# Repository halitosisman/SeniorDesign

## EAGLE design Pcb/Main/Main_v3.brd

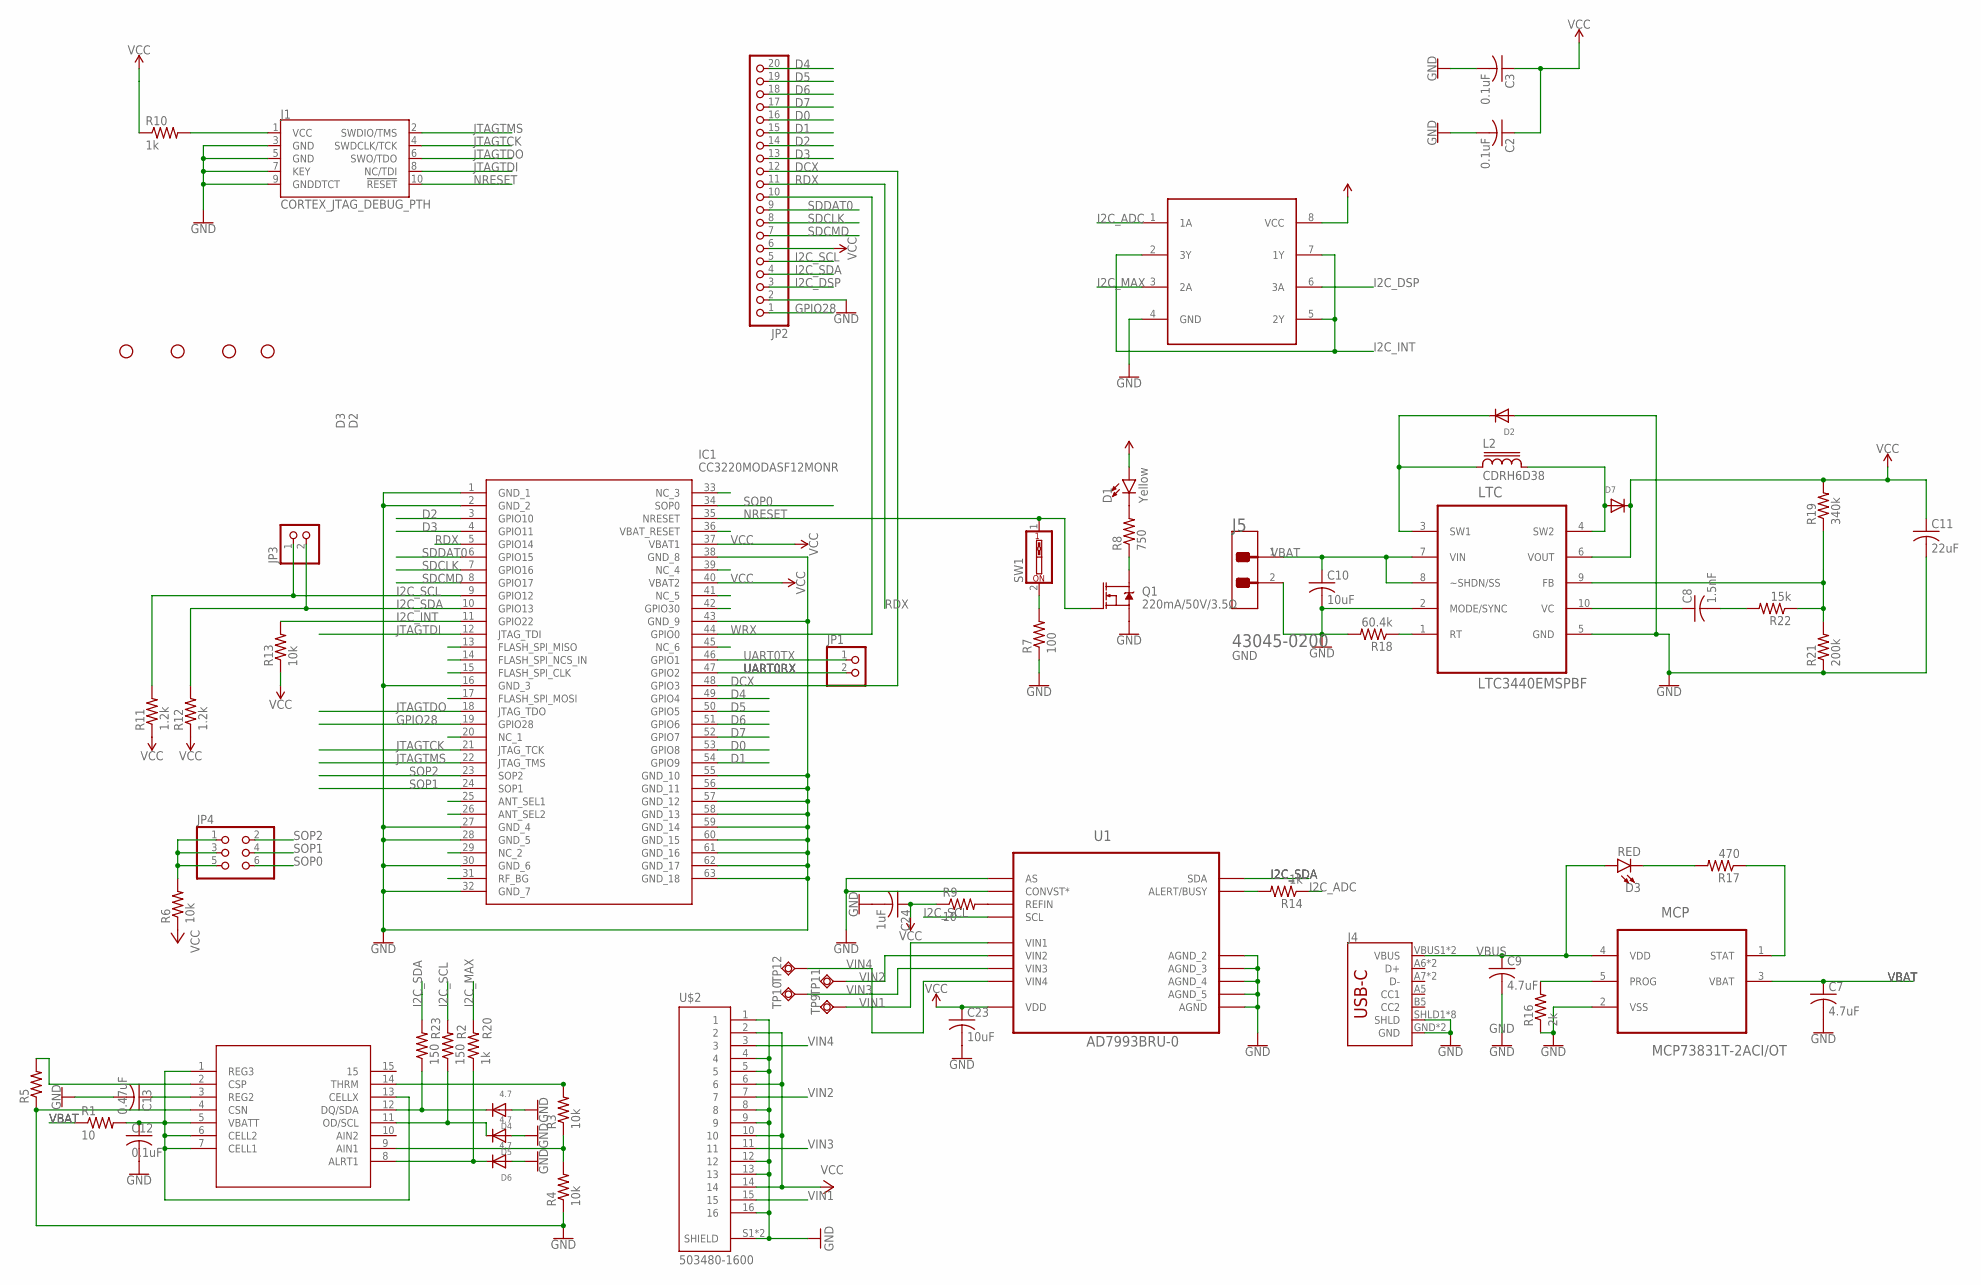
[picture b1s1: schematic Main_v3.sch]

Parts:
74LVC: SOP65P400X110-8N
C2, C3, C12: 0.1uF; C0805
C7, C9: 4.7uF; C0805
C8: 1.5nF; C0805
C10, C23: 10uF; C0805
C11: 22uF; C1210
C13: 0.47uF; C0805
C24: 1uF; C0805
D1: Yellow; LED-0603
D2, D7: DIODESOD-323F; SOD-323F
D3: RED; LED-0603
D4, D5, D6: 4.7; SOD-323F
H1, H2, H3, H4: STAND-OFF
IC1: CC3220MODASF12MONR; CC3220MODASM2MONR
J1: CORTEX_JTAG_DEBUG_PTH; 2X5-PTH-1.27MM
J4: USB_C2-LAYER; USB-C-16P
J5: MOLEX_43045-0200MOLEX_43045-0200_0_0; MOLEX_43045-0200_0
JP1, JP3: PINHD-1X2; 1X02
JP2: PINHD-1X20; 1X20
JP4: PINHD-2X3; 2X03
L2: CDRH6D38; CDRH6D
LTC: LTC3440EMSPBF; SOP50P490X110-10N
MAX: MAX17201G+T; 21-0137I_T1433-1
MCP: MCP73831T-2ACI/OT; SOT95P280X145-5N
Q1: 220mA/50V/3.5Ω; SOT23-3
R1, R9: 10; R0805
R2, R23: 150; R0805
R3, R4, R6, R13: 10k; R0805
R5: R-US_R0805; R0805
R7: 100; R0805
R8: 750; R0805
R10, R14, R20: 1k; R0805
R11, R12: 1.2k; R0805
R16: 2k; R0805
R17: 470; R0805
R18: 60.4k; R0805
R19: 340k; R0805
R21: 200k; R0805
R22: 15k; R0805
SW1: SW_DIP-1; EDG-01
TP9, TP10, TP11, TP12: TPSQTP12R; TP12R
U1: AD7993BRU-0; SOP65P640X120-16N
U$2: 503480-1600; MOLEX_503480-1600

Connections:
D0: IC1.53 (GPIO8), JP2.16
D1: IC1.54 (GPIO9), JP2.15
D2: IC1.3 (GPIO10), JP2.14
D3: IC1.4 (GPIO11), JP2.13
D4: IC1.49 (GPIO4), JP2.20
D5: IC1.50 (GPIO5), JP2.19
D6: IC1.51 (GPIO6), JP2.18
D7: IC1.52 (GPIO7), JP2.17
DCX: IC1.48 (GPIO3), JP2.12
GND: 74LVC.4 (GND), C2.2, C3.2, C7.2, C9.2, C10.2, C11.2, C12.2, C13.2, C23.2, C24.2, D2.A, D4.A, D5.A, D6.A, IC1.1 (GND_1), IC1.2 (GND_2), IC1.16 (GND_3), IC1.27 (GND_4), IC1.28 (GND_5), IC1.30 (GND_6), IC1.32 (GND_7), IC1.38 (GND_8), IC1.43 (GND_9), IC1.55 (GND_10), IC1.56 (GND_11), IC1.57 (GND_12), IC1.58 (GND_13), IC1.59 (GND_14), IC1.60 (GND_15), IC1.61 (GND_16), IC1.62 (GND_17), IC1.63 (GND_18), J1.3 (GND), J1.5 (GND), J1.7 (KEY), J1.9 (GNDDTCT), J4.GND, J4.GND2 (GND), J4.SHLD1 (SHLD), J4.SHLD2 (SHLD), J4.SHLD3 (SHLD), J4.SHLD4 (SHLD), J4.SHLD5 (SHLD), J4.SHLD6 (SHLD), J4.SHLD7 (SHLD), J4.SHLD8 (SHLD), J5.2, JP2.2, LTC.2 (MODE/SYNC), LTC.5 (GND), MAX.4 (CSN), MCP.2 (VSS), Q1.2 (S), R4.1, R5.1, R7.1, R16.1, R18.2, R21.1, U1.1 (AGND_2), U1.2 (AGND_3), U1.3 (AGND_4), U1.4 (AGND_5), U1.11 (AS), U1.12 (CONVST*), U1.16 (AGND), U$2.1, U$2.4, U$2.5, U$2.8, U$2.9, U$2.12, U$2.13, U$2.16, U$2.S1 (SHIELD), U$2.S2 (SHIELD)
GPIO28: IC1.19 (GPIO28), JP2.1
I2C_ADC: 74LVC.1 (1A), R14.1
I2C_DSP: 74LVC.6 (3A), JP2.3
I2C_INT: 74LVC.2 (3Y), 74LVC.5 (2Y), 74LVC.7 (1Y), IC1.11 (GPIO22), R13.2
I2C_MAX: 74LVC.3 (2A), R20.2
I2C_SCL: IC1.9 (GPIO12), JP2.5, JP3.1, R2.2, R11.2, U1.15 (SCL)
I2C_SDA: IC1.10 (GPIO13), JP2.4, JP3.2, R12.2, R23.2, U1.14 (SDA)
JTAGTCK: IC1.21 (JTAG_TCK), J1.4 (SWDCLK/TCK)
JTAGTDI: IC1.12 (JTAG_TDI), J1.8 (NC/TDI)
JTAGTDO: IC1.18 (JTAG_TDO), J1.6 (SWO/TDO)
JTAGTMS: IC1.22 (JTAG_TMS), J1.2 (SWDIO/TMS)
JTAG_R: J1.1 (VCC), R10.2
LTC_CRS: C8.2, R22.2
LTC_FB: LTC.9 (FB), R19.1, R21.2, R22.1
LTC_IND1: D2.C, L2.1, LTC.3 (SW1)
LTC_IND2: D7.A, L2.2, LTC.4 (SW2)
LTC_RT: LTC.1 (RT), R18.1
LTC_VC: C8.1, LTC.10 (VC)
MAX_AIN1: MAX.9 (AIN1), R3.1, R4.2
MAX_CSP: MAX.2 (CSP), R5.2
MAX_INT: D6.C, MAX.8 (ALRT1), R20.1
MAX_REG2: C13.1, MAX.3 (REG2)
MAX_SCL: D5.C, MAX.11 (OD/SCL), R2.1
MAX_SDA: D4.C, MAX.12 (DQ/SDA), R23.1
MAX_THRM: MAX.14 (THRM), R3.2
MAX_VBAT: C12.1, MAX.1 (REG3), MAX.5 (VBATT), MAX.6 (CELL2), MAX.7 (CELL1), MAX.13 (CELLX), R1.2
MPC_LED: D3.C, R17.2
MPC_RPROG: MCP.5 (PROG), R16.2
MPC_STAT: MCP.1 (STAT), R17.1
unnamed: JP4.1, JP4.3, JP4.5, R6.2
unnamed: R9.2, U1.6 (REFIN)
unnamed: R14.2, U1.13 (ALERT/BUSY)
NRESET: IC1.35 (NRESET), J1.10 (!RESET), Q1.1 (G), SW1.1
RDX: IC1.5 (GPIO14), JP2.11
RESET_DIODE: D1.C, R8.2
RESET_MOS: Q1.3 (D), R8.1
RESET_SW1: R7.2, SW1.2
SDCLK: IC1.7 (GPIO16), JP2.8
SDCMD: IC1.8 (GPIO17), JP2.7
SDDAT0: IC1.6 (GPIO15), JP2.9
SOP0: IC1.34 (SOP0), JP4.6
SOP1: IC1.24 (SOP1), JP4.4
SOP2: IC1.23 (SOP2), JP4.2
UART0RX: IC1.47 (GPIO2), JP1.2
UART0TX: IC1.46 (GPIO1), JP1.1
VBAT: C7.1, C10.1, J5.1, LTC.7 (VIN), LTC.8 (~SHDN/SS), MCP.3 (VBAT), R1.1
VBUS: C9.1, D3.A, J4.VBUS1 (VBUS), J4.VBUS2 (VBUS), MCP.4 (VDD)
VCC: 74LVC.8 (VCC), C2.1, C3.1, C11.1, C23.1, C24.1, D1.A, D7.C, IC1.37 (VBAT1), IC1.40 (VBAT2), JP2.6, LTC.6 (VOUT), R6.1, R9.1, R10.1, R11.1, R12.1, R13.1, R19.2, U1.5 (VDD), U$2.2, U$2.6, U$2.10, U$2.14
VIN1: TP9.TP, U1.7 (VIN1), U$2.15
VIN2: TP11.TP, U1.10 (VIN2), U$2.7
VIN3: TP10.TP, U1.8 (VIN3), U$2.11
VIN4: TP12.TP, U1.9 (VIN4), U$2.3
WRX: IC1.44 (GPIO0), JP2.10

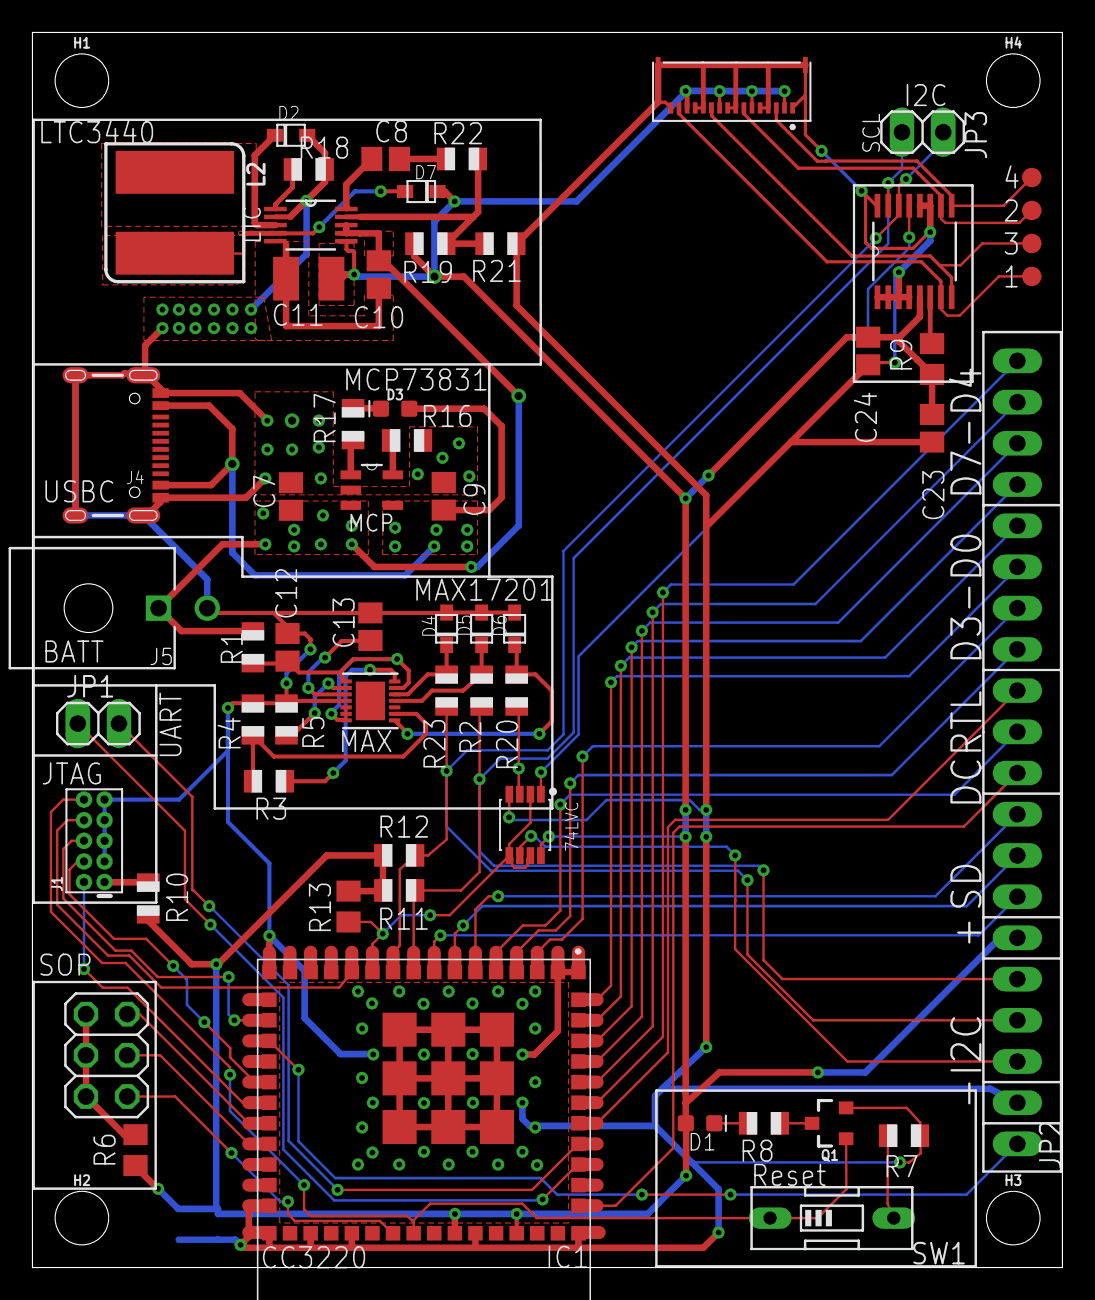
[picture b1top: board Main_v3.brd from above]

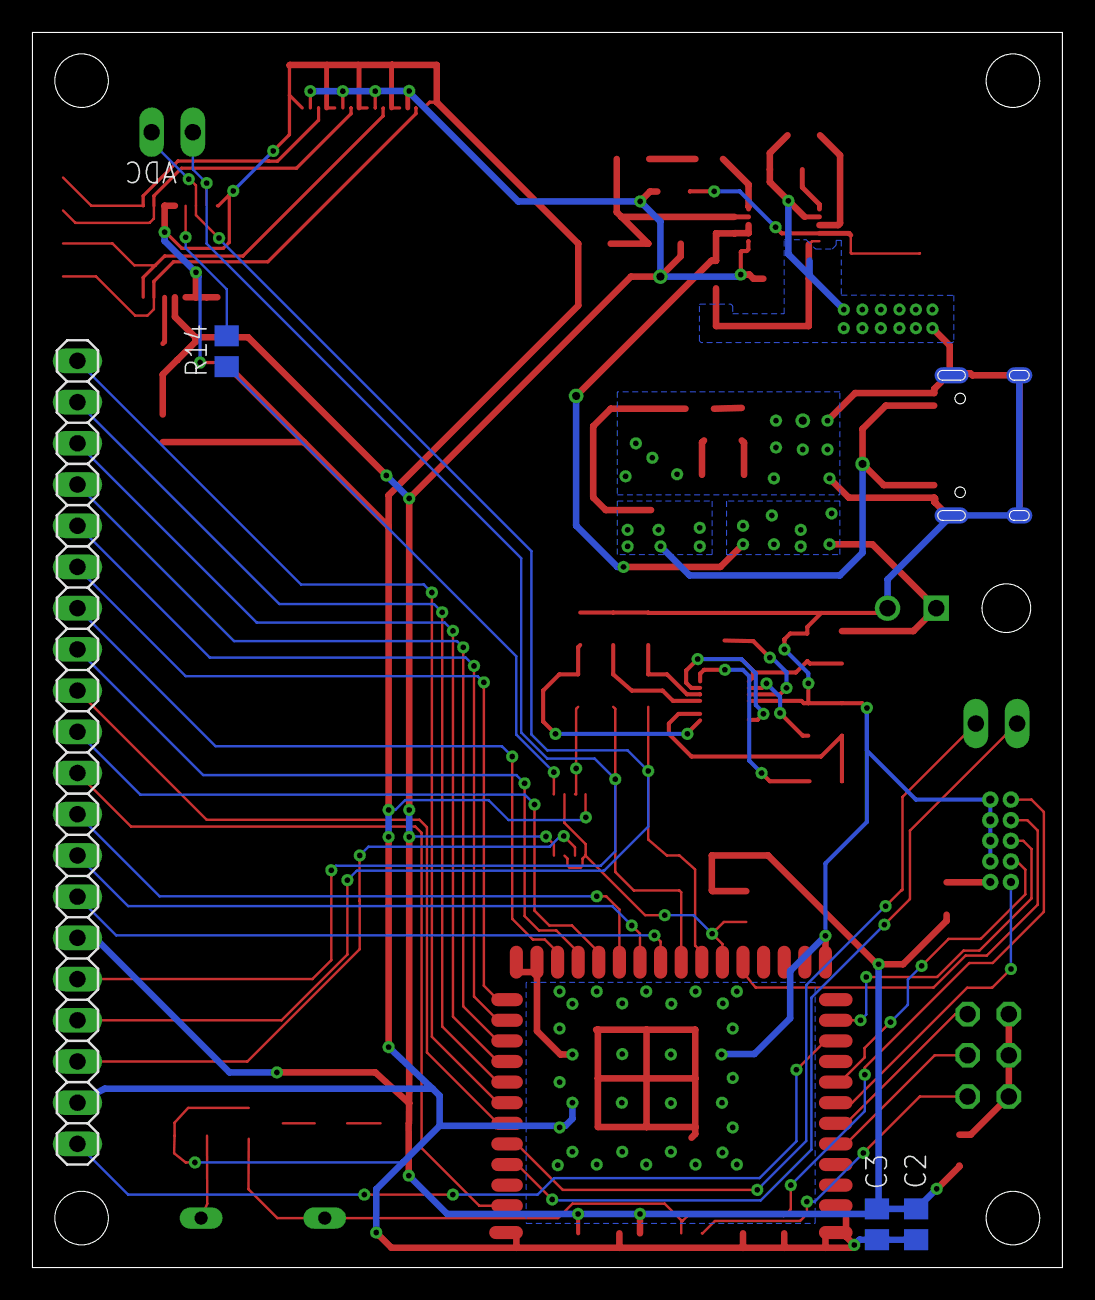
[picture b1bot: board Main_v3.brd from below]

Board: 2 copper layers, 63.5 x 76.1 mm, 65 parts (4 on the bottom side), 63 nets.

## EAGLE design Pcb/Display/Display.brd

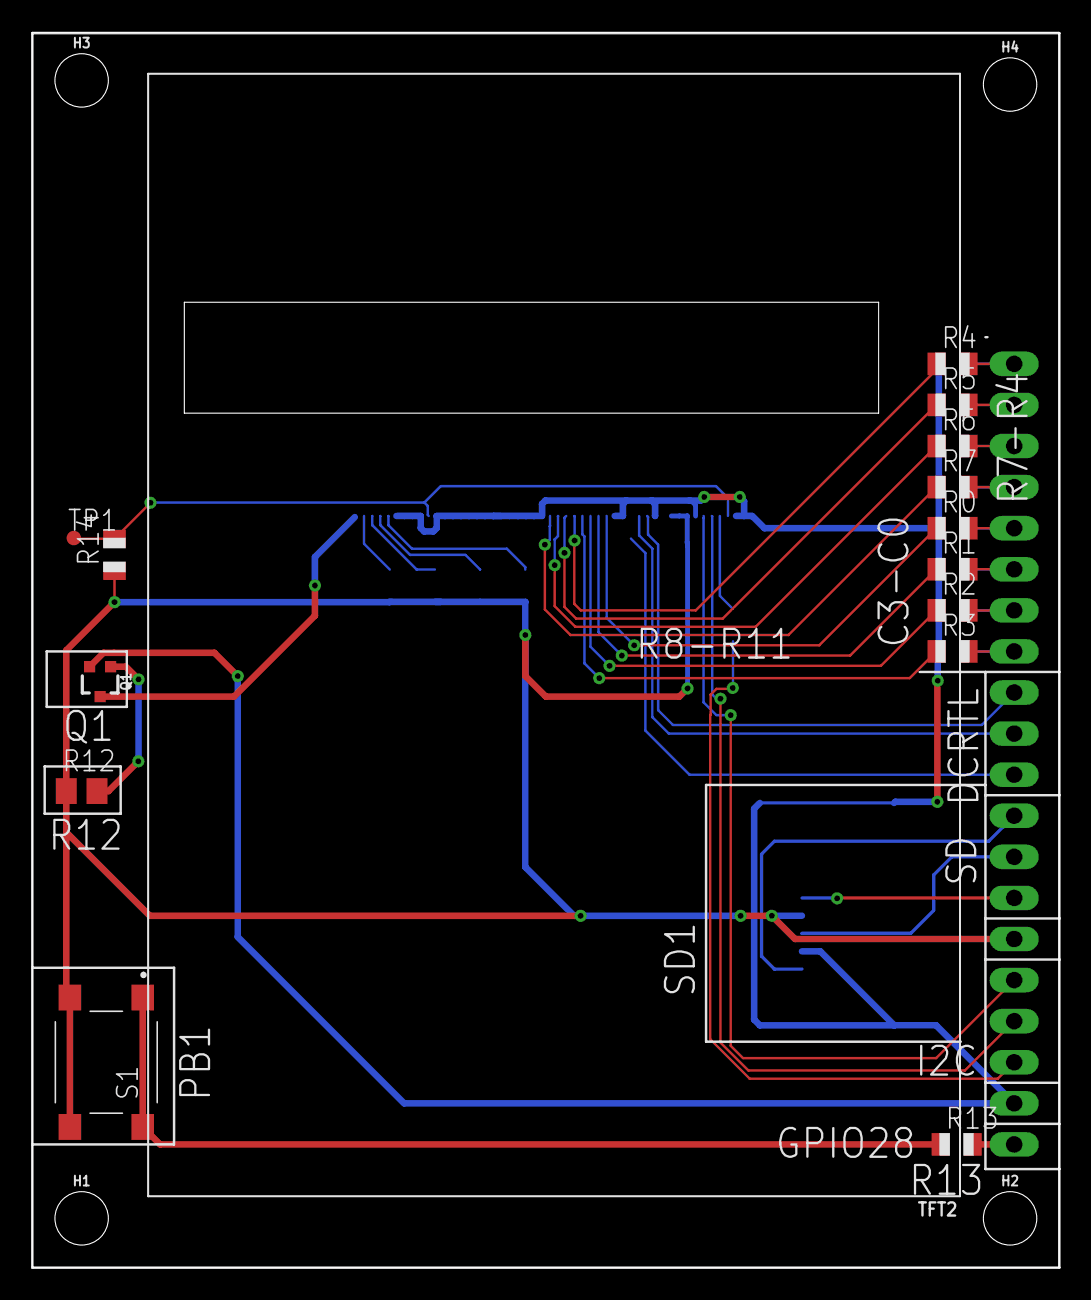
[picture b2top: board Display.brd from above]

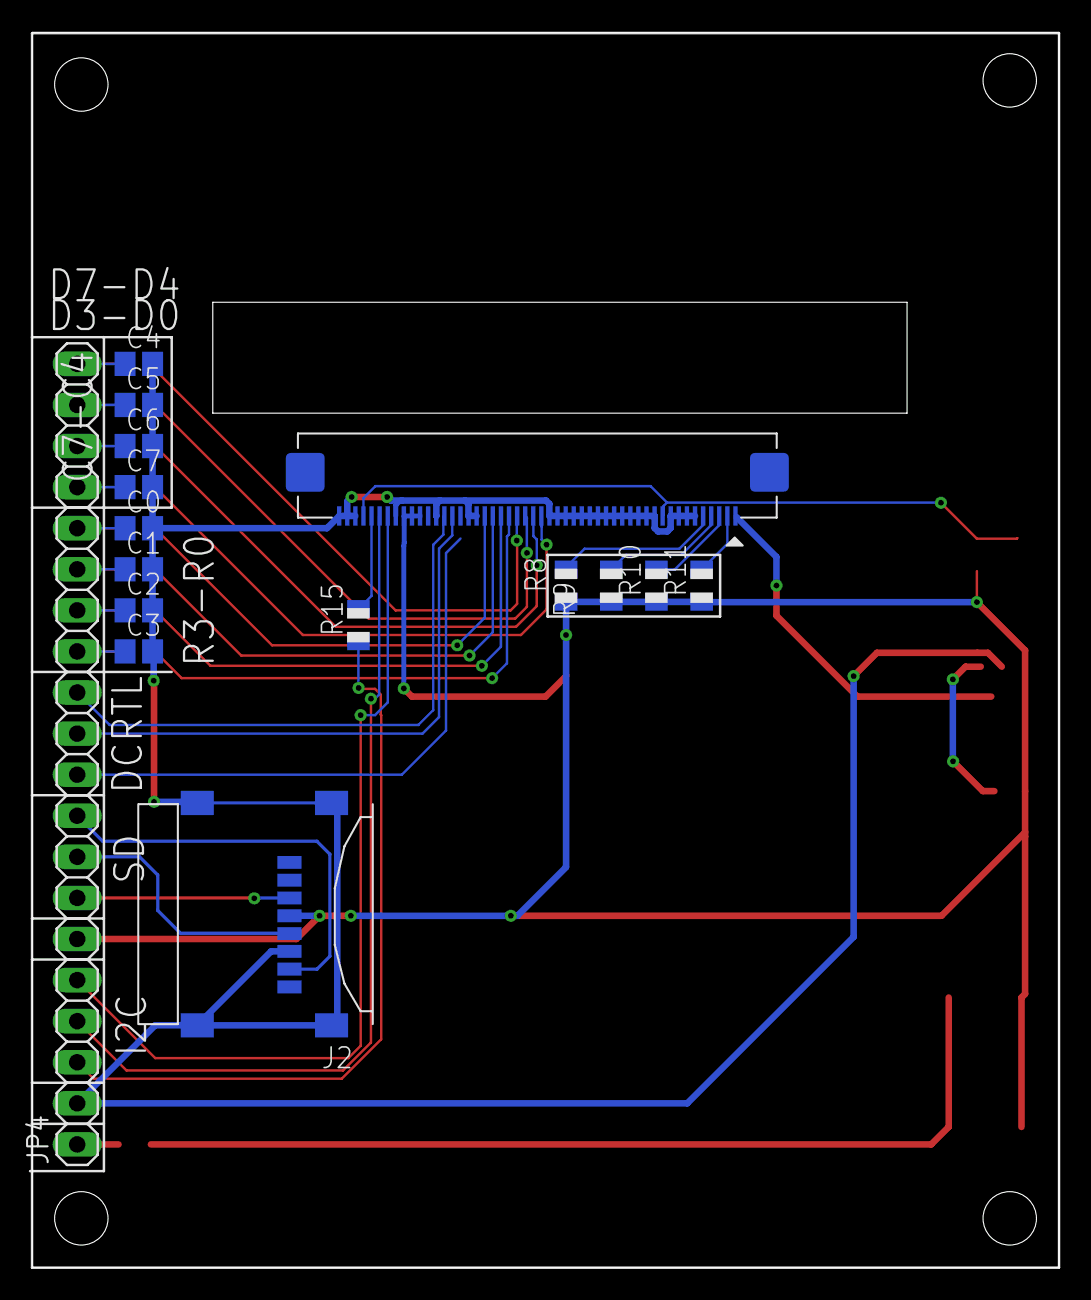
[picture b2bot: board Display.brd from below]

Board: 2 copper layers, 63.5 x 76.4 mm, 34 parts (15 on the bottom side), 37 nets.

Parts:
C0, C1, C2, C3, C4, C5, C6, C7: 10pF; C0805
H1, H2, H3, H4: STAND-OFF
J2: 47219-2001; MOLEX_47219-2001
JP4: Main PCB Header; 1X20
Q1: 310mA/60V/1.6Ω; SOT323
R0, R1, R2, R3, R4, R5, R6, R7, R8, R9, R10, R11, R14: 10; R0805
R12: 2.2k; M0805
R13: 100; R0805
R15: 1k; R0805
S1: B3FS-1000; B3FS1000
TFT2: TFT_CTP28
TP1: TPTP09R; TP09R

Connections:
DB0: C0.1, JP4.16, R0.2
DB1: C1.1, JP4.15, R1.2
DB2: C2.1, JP4.14, R2.2
DB3: C3.1, JP4.13, R3.2
DB4: C4.1, JP4.20, R4.2
DB5: C5.1, JP4.19, R5.2
DB6: C6.1, JP4.18, R6.2
DB7: C7.1, JP4.17, R7.2
DCX: JP4.12, TFT2.37
GND: C0.2, C1.2, C2.2, C3.2, C4.2, C5.2, C6.2, C7.2, J2.6, J2.G1, J2.G2, J2.G3, J2.G4, JP4.2, Q1.2, TFT2.6, TFT2.7, TFT2.8, TFT2.9, TFT2.11, TFT2.12, TFT2.13, TFT2.14, TFT2.15, TFT2.16, TFT2.17, TFT2.18, TFT2.19, TFT2.20, TFT2.21, TFT2.22, TFT2.23, TFT2.24, TFT2.33, TFT2.34, TFT2.38, TFT2.43, TFT2.48, TFT2.49, TFT2.50
GPIO28: JP4.1, R13.2
I2C_INT: JP4.3, R15.1
I2C_SCL: JP4.5, TFT2.44
I2C_SDA: JP4.4, TFT2.45
unnamed: R0.1, TFT2.32
unnamed: R1.1, TFT2.31
unnamed: R2.1, TFT2.30
unnamed: R15.2, TFT2.46
unnamed: R3.1, TFT2.29
unnamed: R4.1, TFT2.28
unnamed: R5.1, TFT2.27
unnamed: R7.1, TFT2.25
unnamed: R6.1, TFT2.26
unnamed: Q1.1, R12.2
R8: R8.2, TFT2.5
R9: R9.2, TFT2.4
R10: R10.2, TFT2.3
R11: R11.2, TFT2.2
R12: Q1.3, TFT2.1
R13: R13.1, S1.1, S1.2
RDX: JP4.11, TFT2.35
RST: R14.2, TFT2.10, TFT2.47, TP1.TP
SD_CLK: J2.5, JP4.8
SD_CMD: J2.3, JP4.7
SD_DAT0: J2.7, JP4.9
VCC: J2.4, JP4.6, R8.1, R9.1, R10.1, R11.1, R12.1, R14.1, S1.3, S1.4, TFT2.40, TFT2.41, TFT2.42
WRX: JP4.10, TFT2.36

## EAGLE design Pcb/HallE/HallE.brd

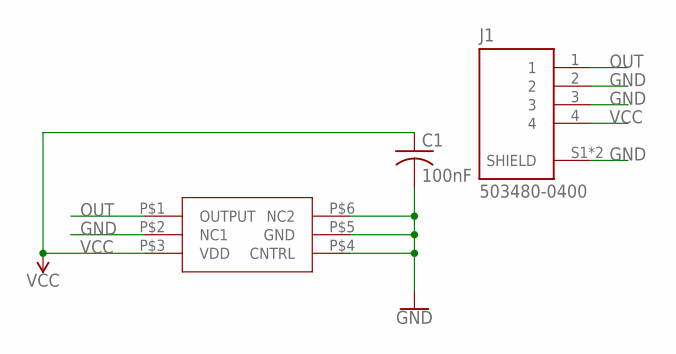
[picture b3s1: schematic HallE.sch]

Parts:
C1: 100nF; C0805
J1: 503480-0400; MOLEX_503480-0400
U$1: AH8503; UDFN-6

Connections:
GND: C1.2, J1.2, J1.3, J1.S1 (SHIELD), J1.S2 (SHIELD), U$1.P$2 (NC1), U$1.P$4 (CNTRL), U$1.P$5 (GND), U$1.P$6 (NC2)
OUT: J1.1, U$1.P$1 (OUTPUT)
VCC: C1.1, J1.4, U$1.P$3 (VDD)

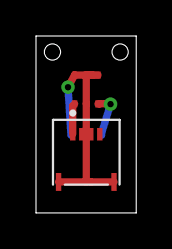
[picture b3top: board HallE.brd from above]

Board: 2 copper layers, 5.6 x 9.8 mm, 3 parts (1 on the bottom side), 3 nets.

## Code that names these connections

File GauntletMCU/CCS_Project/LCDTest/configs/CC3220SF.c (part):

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PowerCC32XX_ParkInfo parkInfo[] = {
/*          PIN                    PARK STATE              PIN ALIAS (FUNCTION)
     -----------------  ------------------------------     -------------------- */
    {PowerCC32XX_PIN01, PowerCC32XX_WEAK_PULL_DOWN_STD}, /* GPIO10              */
    {PowerCC32XX_PIN02, PowerCC32XX_WEAK_PULL_DOWN_STD}, /* GPIO11              */
    {PowerCC32XX_PIN03, PowerCC32XX_WEAK_PULL_DOWN_STD}, /* GPIO12              */
    {PowerCC32XX_PIN04, PowerCC32XX_WEAK_PULL_DOWN_STD}, /* GPIO13              */
    {PowerCC32XX_PIN05, PowerCC32XX_WEAK_PULL_DOWN_STD}, /* GPIO14              */
    {PowerCC32XX_PIN06, PowerCC32XX_WEAK_PULL_DOWN_STD}, /* GPIO15              */
    {PowerCC32XX_PIN07, PowerCC32XX_WEAK_PULL_DOWN_STD}, /* GPIO16              */
    {PowerCC32XX_PIN08, PowerCC32XX_WEAK_PULL_DOWN_STD}, /* GPIO17              */
    {PowerCC32XX_PIN13, PowerCC32XX_WEAK_PULL_DOWN_STD}, /* FLASH_SPI_DIN       */
    {PowerCC32XX_PIN15, PowerCC32XX_WEAK_PULL_DOWN_STD}, /* GPIO22              */
    {PowerCC32XX_PIN16, PowerCC32XX_WEAK_PULL_DOWN_STD}, /* TDI (JTAG DEBUG)    */
    {PowerCC32XX_PIN17, PowerCC32XX_WEAK_PULL_DOWN_STD}, /* TDO (JTAG DEBUG)    */
    {PowerCC32XX_PIN19, PowerCC32XX_WEAK_PULL_DOWN_STD}, /* TCK (JTAG DEBUG)    */
    {PowerCC32XX_PIN20, PowerCC32XX_WEAK_PULL_DOWN_STD}, /* TMS (JTAG DEBUG)    */
    {PowerCC32XX_PIN18, PowerCC32XX_WEAK_PULL_DOWN_STD}, /* GPIO28              */
    {PowerCC32XX_PIN21, PowerCC32XX_WEAK_PULL_DOWN_STD}, /* SOP2                */
    {PowerCC32XX_PIN29, PowerCC32XX_WEAK_PULL_DOWN_STD}, /* ANTSEL1             */
    {PowerCC32XX_PIN30, PowerCC32XX_WEAK_PULL_DOWN_STD}, /* ANTSEL2             */
    {PowerCC32XX_PIN45, PowerCC32XX_WEAK_PULL_DOWN_STD}, /* DCDC_ANA2_SW_P      */
    {PowerCC32XX_PIN50, PowerCC32XX_WEAK_PULL_DOWN_STD}, /* GPIO0               */
    {PowerCC32XX_PIN52, PowerCC32XX_WEAK_PULL_DOWN_STD}, /* RTC_XTAL_N          */
    {PowerCC32XX_PIN53, PowerCC32XX_WEAK_PULL_DOWN_STD}, /* GPIO30              */
    {PowerCC32XX_PIN55, PowerCC32XX_WEAK_PULL_UP_STD},   /* GPIO1 (XDS_UART_RX) */
    {PowerCC32XX_PIN57, PowerCC32XX_WEAK_PULL_UP_STD},   /* GPIO2 (XDS_UART_TX) */
    {PowerCC32XX_PIN58, PowerCC32XX_WEAK_PULL_DOWN_STD}, /* GPIO3               */
    {PowerCC32XX_PIN59, PowerCC32XX_WEAK_PULL_DOWN_STD}, /* GPIO4               */
    {PowerCC32XX_PIN60, PowerCC32XX_WEAK_PULL_DOWN_STD}, /* GPIO5               */
    {PowerCC32XX_PIN61, PowerCC32XX_WEAK_PULL_DOWN_STD}, /* GPIO6               */
    {PowerCC32XX_PIN62, PowerCC32XX_WEAK_PULL_DOWN_STD}, /* GPIO7               */
    {PowerCC32XX_PIN63, PowerCC32XX_WEAK_PULL_DOWN_STD}, /* GPIO8               */
    {PowerCC32XX_PIN64, PowerCC32XX_WEAK_PULL_DOWN_STD}, /* GPIO9               */
};

/*
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
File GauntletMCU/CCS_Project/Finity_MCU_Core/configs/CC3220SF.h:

/*
 * Copyright (c) 2016-2018, Texas Instruments Incorporated
 * All rights reserved.
 *
 * Redistribution and use in source and binary forms, with or without
 * modification, are permitted provided that the following conditions
 * are met:
 *
 * *  Redistributions of source code must retain the above copyright
 *    notice, this list of conditions and the following disclaimer.
 *
 * *  Redistributions in binary form must reproduce the above copyright
 *    notice, this list of conditions and the following disclaimer in the
 *    documentation and/or other materials provided with the distribution.
 *
 * *  Neither the name of Texas Instruments Incorporated nor the names of
 *    its contributors may be used to endorse or promote products derived
 *    from this software without specific prior written permission.
 *
 * THIS SOFTWARE IS PROVIDED BY THE COPYRIGHT HOLDERS AND CONTRIBUTORS "AS IS"
 * AND ANY EXPRESS OR IMPLIED WARRANTIES, INCLUDING, BUT NOT LIMITED TO,
 * THE IMPLIED WARRANTIES OF MERCHANTABILITY AND FITNESS FOR A PARTICULAR
 * PURPOSE ARE DISCLAIMED. IN NO EVENT SHALL THE COPYRIGHT OWNER OR
 * CONTRIBUTORS BE LIABLE FOR ANY DIRECT, INDIRECT, INCIDENTAL, SPECIAL,
 * EXEMPLARY, OR CONSEQUENTIAL DAMAGES (INCLUDING, BUT NOT LIMITED TO,
 * PROCUREMENT OF SUBSTITUTE GOODS OR SERVICES; LOSS OF USE, DATA, OR PROFITS;
 * OR BUSINESS INTERRUPTION) HOWEVER CAUSED AND ON ANY THEORY OF LIABILITY,
 * WHETHER IN CONTRACT, STRICT LIABILITY, OR TORT (INCLUDING NEGLIGENCE OR
 * OTHERWISE) ARISING IN ANY WAY OUT OF THE USE OF THIS SOFTWARE,
 * EVEN IF ADVISED OF THE POSSIBILITY OF SUCH DAMAGE.
 */
/** ============================================================================
 *  @file       C3220SF_LAUNCHXL.h
 *
 *  @brief      CC3220 Board Specific APIs
 *
 *  The CC3220SF_LAUNCHXL header file should be included in an application as
 *  follows:
 *  @code
 *  #include <CC3220SF_LAUNCHXL.h>
 *  @endcode
 *
 *  ============================================================================
 */
#ifndef __CC3220SF_LAUNCHXL_H
#define __CC3220SF_LAUNCHXL_H


#include "stdint.h"
#include <ti/drivers/I2C.h>

/* Common interface includes                                                 */
#include "tasks/net_task/network_if.h"
#include "util/uart_term.h"


#ifdef __cplusplus
extern "C" {
#endif

UART_Handle uart_debug;

typedef enum CC3220SF_LAUNCHXL_SPIName {
    CC3220SF_LAUNCHXL_SPI0 = 0,

    CC3220SF_LAUNCHXL_SPICOUNT
} CC3220SF_LAUNCHXL_SPIName;

typedef enum {
    GPIO_RDX = 0,
    GPIO_WRX,
    GPIO_DCX,
    GPIO_D7,
    GPIO_D6,
    GPIO_D5,
    GPIO_D4,
    GPIO_D3,
    GPIO_D2,
    GPIO_D1,
    GPIO_D0,
    GPIO_I2C_Int,
    GPIO_Pin_Count
} GPIO_Settings;

void i2c_int_callback(uint_least8_t index);

extern void CC3220SF_LAUNCHXL_initGeneral(void);

#ifdef __cplusplus
}
#endif

#endif /* __CC3220SF_LAUNCHXL_H */

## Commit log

2020-03-09 Added Pcb design files
2020-04-03 Updated PCB files and ported some of the graphics functions. The graphics changes are not tested yet.
2020-04-03 First draft of Graphics Port. Also moved all peripheral initializations to a single function where they probably belong.
2020-04-12 Everything works again.
2020-04-13 Deleted example projects. Base TI graphics functionality implemented.
2020-04-18 Added LCD functionality into core project and started work on GUI layer.
2020-04-19 2/3 GUI prototypes.
2020-04-20 Began I2C thread work
2020-04-20 GUI stuff working and first draft of ADC drivers.
2020-04-21 First contact between I2C and ADC.
2020-04-21 Added a picture of the circuitboard schematic
2020-04-22 ADC over I2C functionality implemented.
2020-04-22 Added some things I forgot to handle earlier.
2020-04-22 Ongoing work on i2c and gui task integration.
2020-04-23 Project compiles now. Still need to integrate MQTT stuff.
2020-04-24 Minor indenting changes.
2020-04-24 Continued work on state machine.
2020-04-25 More integration stuff. It compiles without warnings.
2020-04-25 First Draft of integrated code. A remaining GUI element still needs to be implemented.
2020-04-26 Fixed I2C_open fault, made the taskhandles get properly referenced from within threads. God I wish TI would fix their driver bugs.
2020-04-27 Got I2C alerts working.
2020-04-27 I2C integration finished. Networking integration started.
2020-04-28 Pretty sure the cause of bugs is TI's signature undocumented POSIX behaviors.
2020-04-28 Hopefully everything works fine in POSIX form now.
2020-04-29 It actually works
2020-04-29 Enhanced GUI v1 added.
2020-04-29 Added some of Daniel's stuff and cleaned up a load of other unused stuff.
2020-04-29 Ongoing work on removing hardcoded GUI values and allowing has-a relationships between GUI windows.
2020-04-29 More GUI work.
2020-04-30 First Draft of the fancy spanking GUI.
2020-04-30 Most bugs ironed out. GUI is functional.
2020-04-30 I added a space
2020-05-04 Added some stuff to the 3d mockup file and a bunch of comments to the main project.
2020-05-04 Finished Documenting Peter's stuff.
2020-05-04 Added Daniel's comments.
2020-05-04 Some cleanup.

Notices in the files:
GauntletMCU/CCS_Project/LCDTest/configs/CC3220SF.c:
Copyright (c) 2016-2019, Texas Instruments Incorporated
All rights reserved.
parts and their libraries:
SparkFun-DiscreteSemi: Licensing: Creative Commons ShareAlike 4.0 International - https://creativecommons.org/licenses/by-sa/4.0
COPYRIGHT: Copyright (C) 2018 Accelerated Designs. All rights reserved
